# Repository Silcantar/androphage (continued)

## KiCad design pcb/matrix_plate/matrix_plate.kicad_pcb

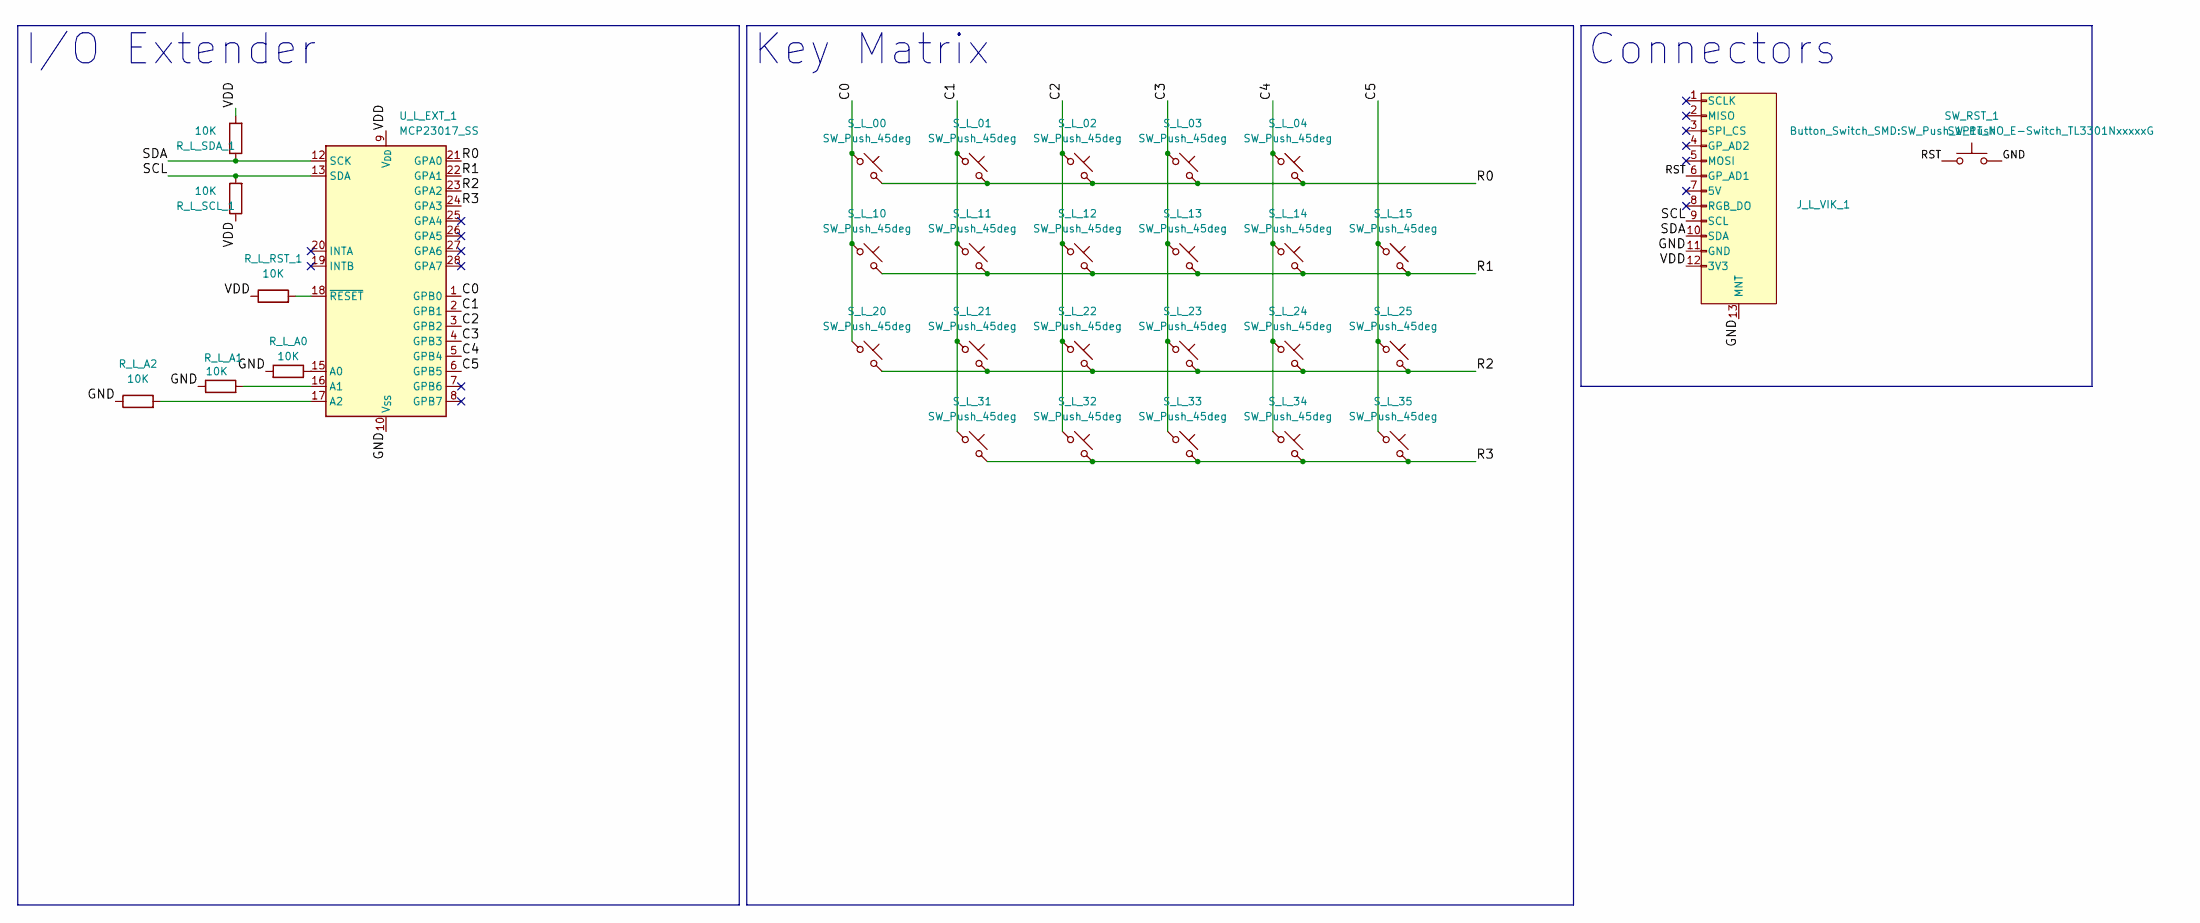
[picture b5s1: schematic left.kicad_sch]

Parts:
J_L_VIK_1: vik-module-connector; vik-module-connector-horizontal
R_L_A0, R_L_A1, R_L_A2: 10K; R_0805_2012Metric_Pad1.20x1.40mm_HandSolder
R_L_RST_1: 10K; R_0805_2012Metric_Pad1.20x1.40mm_HandSolder
R_L_SCL_1: 10K; R_0805_2012Metric_Pad1.20x1.40mm_HandSolder
R_L_SDA_1: 10K; R_0805_2012Metric_Pad1.20x1.40mm_HandSolder
SW_RST_1: SW_Push; SW_Push_1P1T_NO_E-Switch_TL3301NxxxxxG
S_L_00, S_L_01, S_L_02, S_L_03, S_L_04, S_L_10, S_L_11, S_L_12, S_L_13, S_L_14, S_L_15, S_L_20, S_L_21, S_L_22, S_L_23, S_L_24, S_L_25, S_L_31, S_L_32, S_L_33, S_L_34, S_L_35: SW_Push_45deg; SW_GLP_Kailh_Choc_V1V2_HotSwap_PTH
U_L_EXT_1: MCP23017_SS; SSOP-28_5.3x10.2mm_P0.65mm

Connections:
/Left/C0: S_L_00.1, S_L_10.1, S_L_20.1, U_L_EXT_1.1 (GPB0)
/Left/C1: S_L_01.1, S_L_11.1, S_L_21.1, S_L_31.1, U_L_EXT_1.2 (GPB1)
/Left/C2: S_L_02.1, S_L_12.1, S_L_22.1, S_L_32.1, U_L_EXT_1.3 (GPB2)
/Left/C3: S_L_03.1, S_L_13.1, S_L_23.1, S_L_33.1, U_L_EXT_1.4 (GPB3)
/Left/C4: S_L_04.1, S_L_14.1, S_L_24.1, S_L_34.1, U_L_EXT_1.5 (GPB4)
/Left/C5: S_L_15.1, S_L_25.1, S_L_35.1, U_L_EXT_1.6 (GPB5)
/Left/GND: J_L_VIK_1.11 (GND), J_L_VIK_1.13 (MNT), R_L_A0.2, R_L_A1.1, R_L_A2.1, SW_RST_1.2, U_L_EXT_1.10 (V_{SS})
/Left/R0: S_L_00.2, S_L_01.2, S_L_02.2, S_L_03.2, S_L_04.2, U_L_EXT_1.21 (GPA0)
/Left/R1: S_L_10.2, S_L_11.2, S_L_12.2, S_L_13.2, S_L_14.2, S_L_15.2, U_L_EXT_1.22 (GPA1)
/Left/R2: S_L_20.2, S_L_21.2, S_L_22.2, S_L_23.2, S_L_24.2, S_L_25.2, U_L_EXT_1.23 (GPA2)
/Left/R3: S_L_31.2, S_L_32.2, S_L_33.2, S_L_34.2, S_L_35.2, U_L_EXT_1.24 (GPA3)
/Left/RST: J_L_VIK_1.6 (GP_AD1), SW_RST_1.1
/Left/SCL: J_L_VIK_1.9 (SCL), R_L_SCL_1.2, U_L_EXT_1.13 (SDA)
/Left/SDA: J_L_VIK_1.10 (SDA), R_L_SDA_1.1, U_L_EXT_1.12 (SCK)
/Left/VDD: J_L_VIK_1.12 (3V3), R_L_RST_1.1, R_L_SCL_1.1, R_L_SDA_1.2, U_L_EXT_1.9 (V_{DD})
unnamed: R_L_A0.1, U_L_EXT_1.15 (A0)
unnamed: R_L_A1.2, U_L_EXT_1.16 (A1)
unnamed: R_L_A2.2, U_L_EXT_1.17 (A2)
unnamed: R_L_RST_1.2, U_L_EXT_1.18 (~RESET)

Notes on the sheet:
Connectors
Key Matrix
I/O Extender

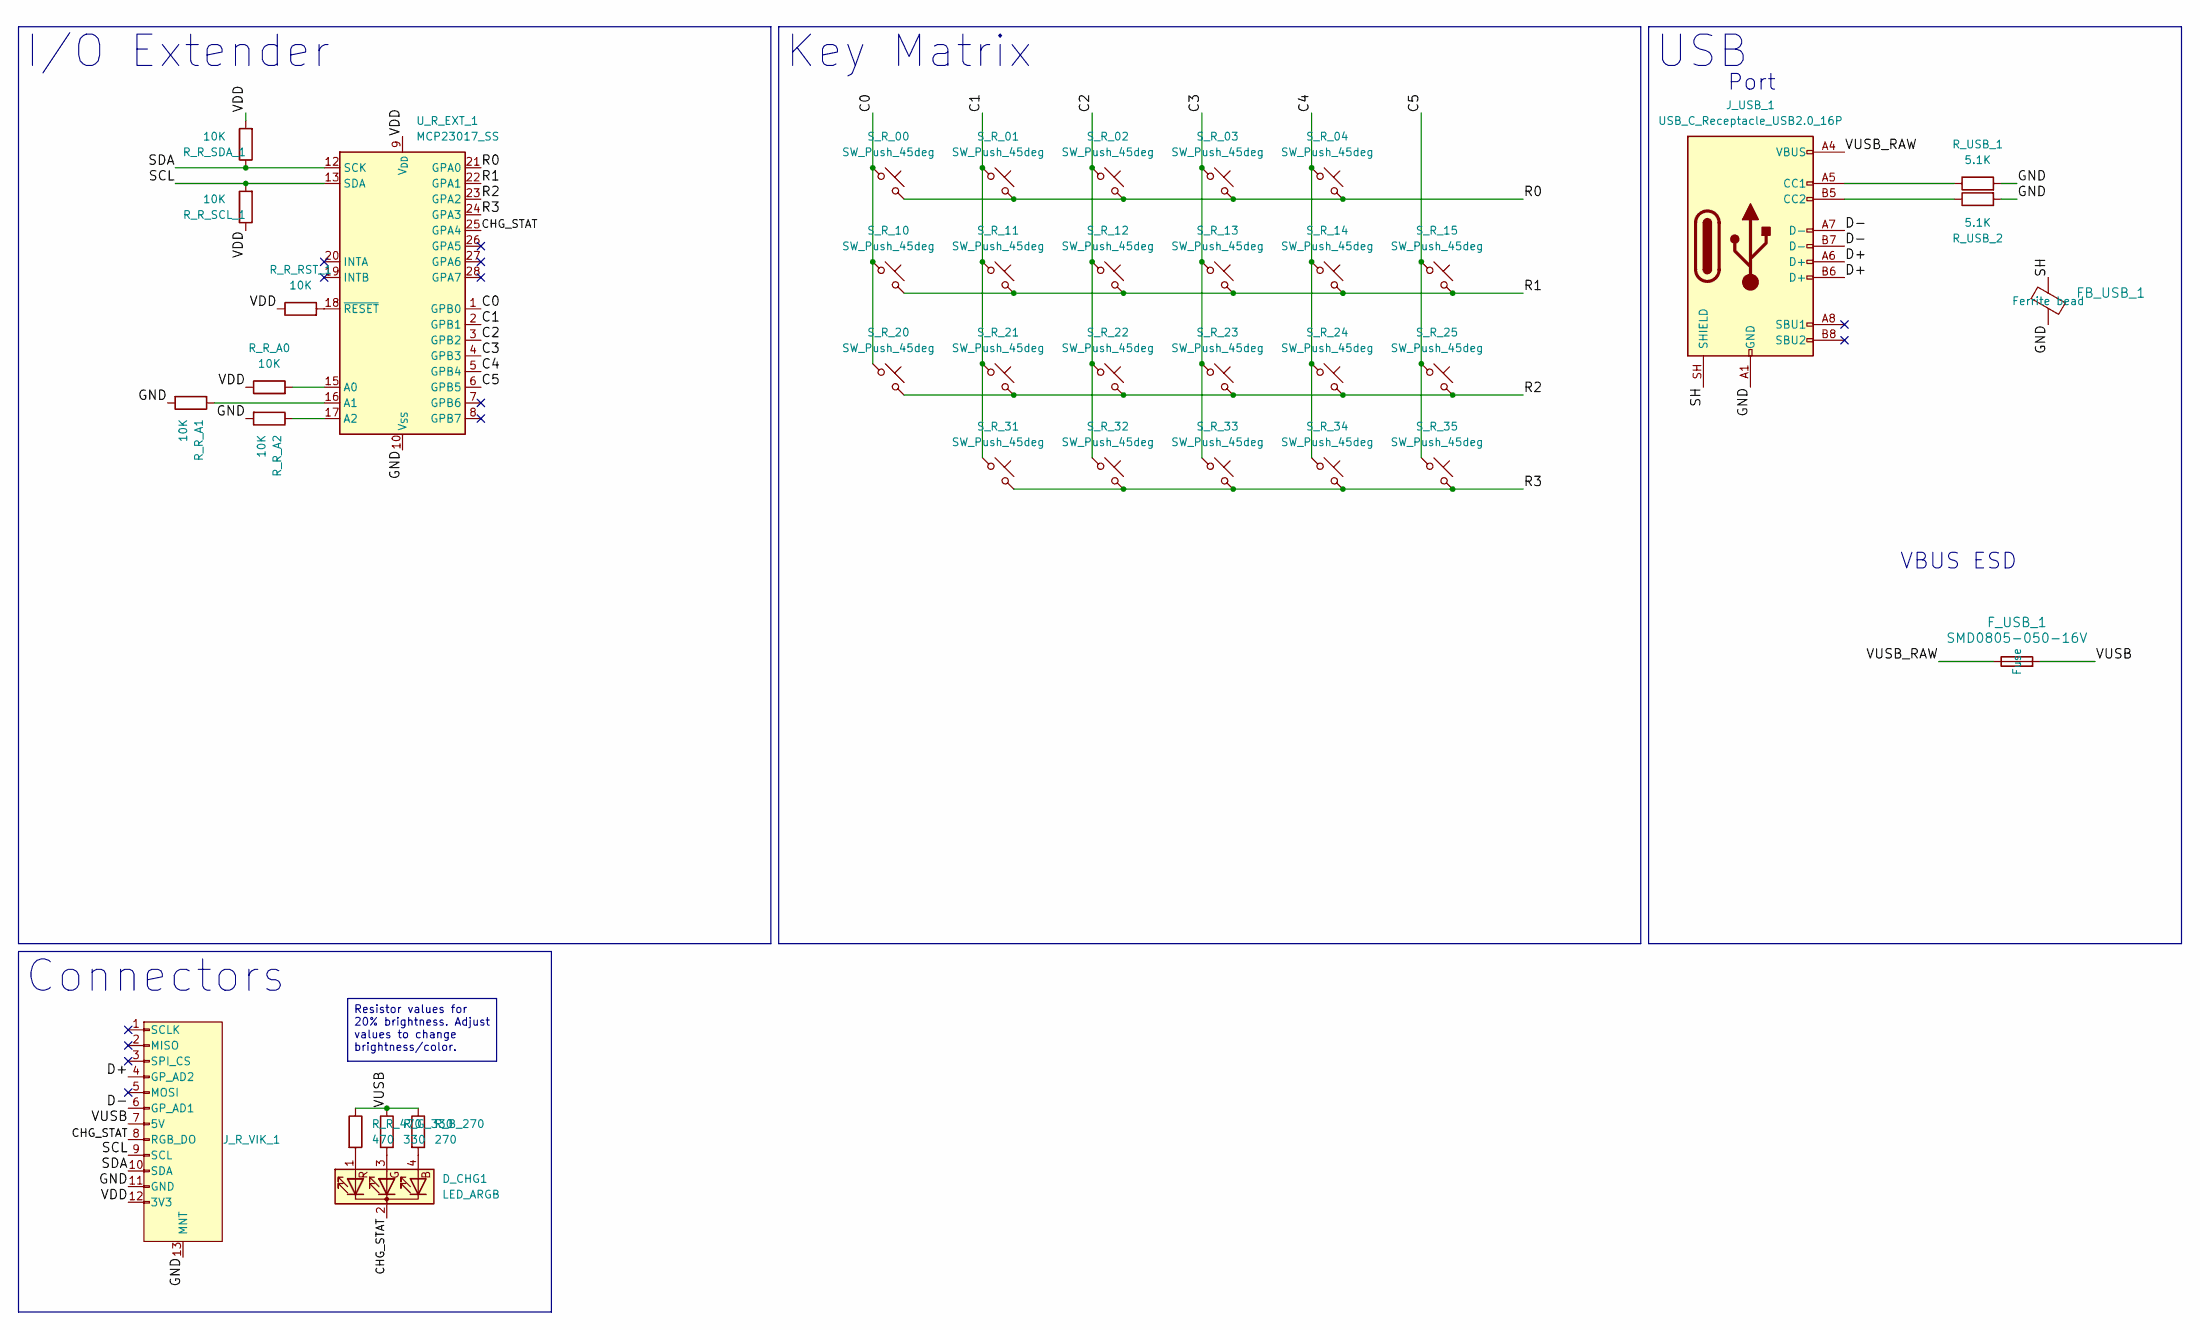
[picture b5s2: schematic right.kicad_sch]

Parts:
D_CHG1: LED_ARGB; LED_Kingbright_APFA3010_3x1.5mm_Horizontal
FB_USB_1: L_0805_2012Metric_Pad1.05x1.20mm_HandSolder; LCSC Part Number C21286
F_USB_1: SMD0805-050-16V; Fuse_0805_2012Metric_Pad1.15x1.40mm_HandSolder; Manufacturer Part Number SMD0805-050-16V; LCSC Part Number C2833485
J_R_VIK_1: vik-module-connector; vik-module-connector-horizontal
J_USB_1: USB_C_Receptacle_USB2.0_16P; USB_C_Receptacle_HRO_TYPE-C-31-M-12
R_B_270: 270; R_0805_2012Metric_Pad1.20x1.40mm_HandSolder
R_G_330: 330; R_0805_2012Metric_Pad1.20x1.40mm_HandSolder
R_R_470: 470; R_0805_2012Metric_Pad1.20x1.40mm_HandSolder
R_R_A0, R_R_A1, R_R_A2: 10K; R_0805_2012Metric_Pad1.20x1.40mm_HandSolder
R_R_RST_1: 10K; R_0805_2012Metric_Pad1.20x1.40mm_HandSolder
R_R_SCL_1: 10K; R_0805_2012Metric_Pad1.20x1.40mm_HandSolder
R_R_SDA_1: 10K; R_0805_2012Metric_Pad1.20x1.40mm_HandSolder
R_USB_1, R_USB_2: 5.1K; R_0805_2012Metric_Pad1.20x1.40mm_HandSolder
S_R_00, S_R_01, S_R_02, S_R_03, S_R_04, S_R_10, S_R_11, S_R_12, S_R_13, S_R_14, S_R_15, S_R_20, S_R_21, S_R_22, S_R_23, S_R_24, S_R_25, S_R_31, S_R_32, S_R_33, S_R_34, S_R_35: SW_Push_45deg; SW_GLP_Kailh_Choc_V1V2_HotSwap_PTH
U_R_EXT_1: MCP23017_SS; SSOP-28_5.3x10.2mm_P0.65mm

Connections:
/Right/C0: S_R_00.1, S_R_10.1, S_R_20.1, U_R_EXT_1.1 (GPB0)
/Right/C1: S_R_01.1, S_R_11.1, S_R_21.1, S_R_31.1, U_R_EXT_1.2 (GPB1)
/Right/C2: S_R_02.1, S_R_12.1, S_R_22.1, S_R_32.1, U_R_EXT_1.3 (GPB2)
/Right/C3: S_R_03.1, S_R_13.1, S_R_23.1, S_R_33.1, U_R_EXT_1.4 (GPB3)
/Right/C4: S_R_04.1, S_R_14.1, S_R_24.1, S_R_34.1, U_R_EXT_1.5 (GPB4)
/Right/C5: S_R_15.1, S_R_25.1, S_R_35.1, U_R_EXT_1.6 (GPB5)
/Right/CHG_STAT: D_CHG1.2 (K), J_R_VIK_1.8 (RGB_DO), U_R_EXT_1.25 (GPA4)
/Right/D+: J_R_VIK_1.4 (GP_AD2), J_USB_1.A6 (D+), J_USB_1.B6 (D+)
/Right/D-: J_R_VIK_1.6 (GP_AD1), J_USB_1.A7 (D-), J_USB_1.B7 (D-)
/Right/GND: FB_USB_1.2, J_R_VIK_1.11 (GND), J_R_VIK_1.13 (MNT), J_USB_1.A1 (GND), J_USB_1.A12 (GND), J_USB_1.B1 (GND), J_USB_1.B12 (GND), R_R_A1.2, R_R_A2.2, R_USB_1.2, R_USB_2.2, U_R_EXT_1.10 (V_{SS})
/Right/R0: S_R_00.2, S_R_01.2, S_R_02.2, S_R_03.2, S_R_04.2, U_R_EXT_1.21 (GPA0)
/Right/R1: S_R_10.2, S_R_11.2, S_R_12.2, S_R_13.2, S_R_14.2, S_R_15.2, U_R_EXT_1.22 (GPA1)
/Right/R2: S_R_20.2, S_R_21.2, S_R_22.2, S_R_23.2, S_R_24.2, S_R_25.2, U_R_EXT_1.23 (GPA2)
/Right/R3: S_R_31.2, S_R_32.2, S_R_33.2, S_R_34.2, S_R_35.2, U_R_EXT_1.24 (GPA3)
/Right/SCL: J_R_VIK_1.9 (SCL), R_R_SCL_1.2, U_R_EXT_1.13 (SDA)
/Right/SDA: J_R_VIK_1.10 (SDA), R_R_SDA_1.1, U_R_EXT_1.12 (SCK)
/Right/SH: FB_USB_1.1, J_USB_1.SH (SHIELD)
/Right/VDD: J_R_VIK_1.12 (3V3), R_R_A0.1, R_R_RST_1.1, R_R_SCL_1.1, R_R_SDA_1.2, U_R_EXT_1.9 (V_{DD})
/Right/VUSB: F_USB_1.2, J_R_VIK_1.7 (5V), R_B_270.1, R_G_330.1, R_R_470.1
/Right/VUSB_RAW: F_USB_1.1, J_USB_1.A4 (VBUS), J_USB_1.A9 (VBUS), J_USB_1.B4 (VBUS), J_USB_1.B9 (VBUS)
unnamed: D_CHG1.4 (BA), R_B_270.2
unnamed: D_CHG1.3 (GA), R_G_330.2
unnamed: D_CHG1.1 (RA), R_R_470.2
unnamed: J_USB_1.A5 (CC1), R_USB_1.1
unnamed: J_USB_1.B5 (CC2), R_USB_2.1
unnamed: R_R_A0.2, U_R_EXT_1.15 (A0)
unnamed: R_R_A1.1, U_R_EXT_1.16 (A1)
unnamed: R_R_A2.1, U_R_EXT_1.17 (A2)
unnamed: R_R_RST_1.2, U_R_EXT_1.18 (~RESET)

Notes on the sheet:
VBUS ESD
Port
Connectors
USB
I/O Extender
Key Matrix
Resistor values for 20% brightness. Adjust values to change brightness/color.

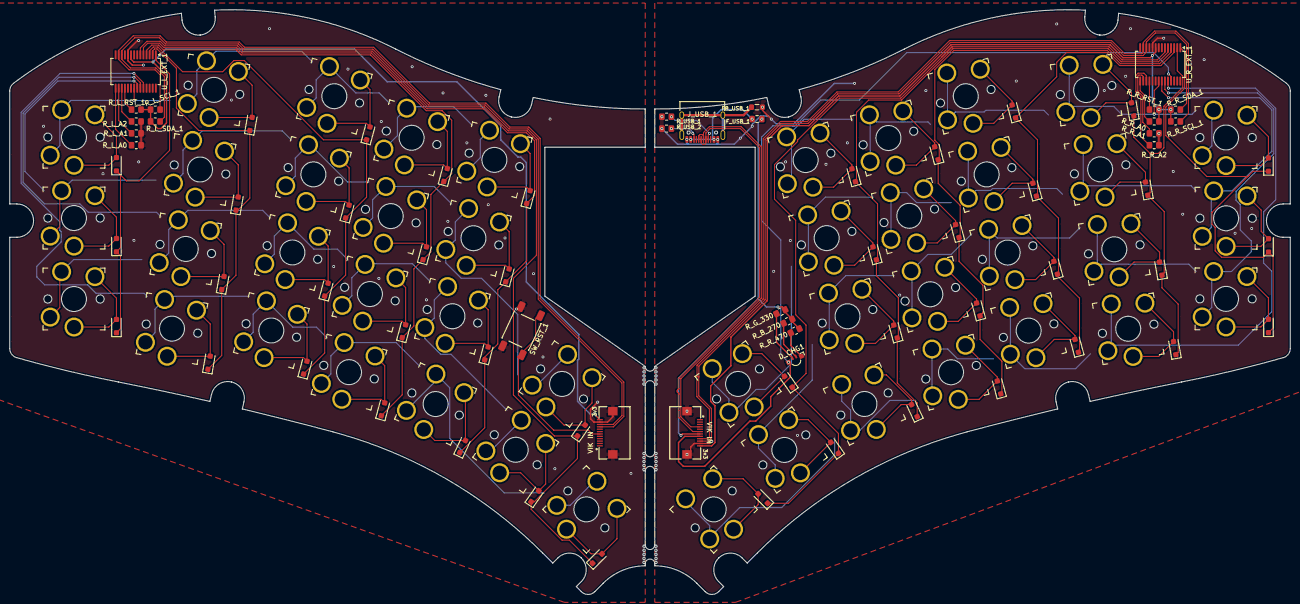
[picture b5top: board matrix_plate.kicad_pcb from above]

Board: 2 copper layers, 269.2 x 122.9 mm, 70 parts (0 on the bottom side), 48 nets.

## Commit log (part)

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2025-11-24 Initial Commit.
2025-11-27 Work on PCBs.
2025-11-28 Replace KB2040 with XIAO nRF, work on PCB routing.
2025-12-10 Clean up folder structure.
2025-12-11 Work on case.
2025-12-11 Create VIK hat for Seeed Xiao nRF.
2025-12-13 Tentatively finish PCB design.
2025-12-16 Work on mechanical design.
2025-12-18 Change VIK submodule to the dev branch of my fork to include the modules developed for this project.
2025-12-18 Change license from GPLv3 to CERN-OHL-Sv2.
2025-12-18 Parametrize mechanical design.
2025-12-19 - Tentatively finish switch and top plates. - Add BOSL as submodule.
2025-12-19 Rename BOSL to BOSL2.
2025-12-19 Refactor basically everything.
2025-12-30 Expose plate sketch points as functions.
2026-01-01 Updated VIK.
2026-01-06 Refactor parameters to not use objects.
2026-01-07 Finish refactoring.
2026-01-07 More refactoring.
2026-01-10 Remove BOSL2 submodule.
2026-01-12 Increase tent to 7 degrees.
2026-01-20 Remove BOSL again.
2026-01-23 Add thumb cluster notch to frame.
2026-01-23 Clean up CAD files.
2026-01-23 Work on path framework to reconcile plates with frame.
2026-01-23 Update documentation.
2026-01-24 Finish the necessary parts of the path library.
2026-01-24 Update BOM.
2026-01-25 Remove cad/library folder and re-add it as a submodule.
2026-01-25 Fix hard-coded notch cutter dimension.
2026-01-25 Move items to openscad_library.
2026-01-25 Start converting bottom plate to use path library.
2026-01-25 Rename some hinge parameters.
2026-01-25 Start refactoring to re-enable Configurator, reduce file size, and improve modularity.
2026-01-26 Move global declarations to separate file.
2026-01-26 Move parameter calculations to separate file.
2026-01-26 Start updating component files with new structure.
2026-01-26 Add missing parameters to objects.
2026-01-26 Update more components with new structure.
2026-01-27 Change indentation to spaces.
2026-01-27 Minor reorganization of definitions.
2026-01-27 Update library.
2026-01-27 More minor definition reorganization.
2026-01-27 Update banner image.
2026-01-28 Add quote to readme.
2026-01-28 Add cluster cutout parameter.
2026-01-28 Unify plate and PCB code.
2026-01-28 Start updating main files with new structure.
2026-01-29 Change from using "use" to import components to using "include". Remove circular includes.
2026-01-29 Update components to reflect the use of "include" rather than "use".
2026-01-30 Add OpenSCAD configurator JSON.
2026-01-30 Revert to non-object parameters.
2026-02-01 Fix misalignment of plates and frame.
2026-02-01 Clean up dead code.
2026-02-01 Add cutouts to plates for trackball & sensor.
2026-02-01 Fix cutouts in center block for hinges and top plate.
2026-02-01 Adjust magnetic connector placement, add cutout to PCB and switch plate.
2026-02-01 Add fillets to LED holes.
2026-02-02 Clean up dead code in androphage.scad.
2026-02-02 Fix key cutouts in hinge.
2026-02-03 Add USB cutout to MCU.
2026-02-03 Remove KLP Lamé submodule.
2026-02-03 Fix frame height.
2026-02-03 Remove switch STL.
2026-02-03 Remove KLP Lamé from .gitmodules.
2026-02-03 Add keycaps submodule.
2026-02-03 Update keycaps submodule.
2026-02-03 Start rewriting key placement module.
2026-02-08 Add compile script.
2026-02-08 Update keycaps and library submodules.
2026-02-09 Update submodules.
2026-02-09 Rewrite switch and keycap placement code.
2026-02-10 Add PCB submodules.
2026-02-10 Move old PCB files to "old" folder.
2026-02-11 Re-create KiCAD project.
2026-02-11 - Adapt nrfmicro schematic for control and power components. - Copy key matrix schematics from old KiCAD project.
2026-02-11 Complete preliminary PCB schematic.
2026-02-12 Add KiCAD backup files to gitignore.
2026-02-12 Add option to export switch plate sketch DXF for PCB design.
2026-02-12 Start PCB layout.
2026-02-12 Move old KiCAD files to old folder.
2026-02-12 Start adding support for column splay.
2026-02-16 Add BOSL2 as submodule.
2026-02-18 Add compiles OpenSCAD files to gitignore.
2026-02-18 Update BOSL2.
2026-02-18 Update compile.sh.
2026-02-18 Start BOSL-based plate and frame outline.
2026-02-19 Add ergogen json file.
2026-02-19 Create script for converting Ergogen YAML to OpenSCAD.
2026-02-20 Start PythonSCAD project.
2026-02-22 Refine battery component; start BTU component.
2026-02-23 Add .venv to gitignore.
2026-02-23 Start cadQuery project.
2026-02-24 Start Build123d project.
2026-02-24 Move OpenSCAD project to corresponding folder.
2026-02-24 Rename build123d to cad.
2026-02-24 Finish battery and BTU components; start key placement module.
2026-02-26 Start writing code to convert ergogen yaml to key placement.
2026-02-27 Work on key placement.
2026-03-03 Work on key locations.
2026-03-04 Remove old submodule folders.
2026-03-04 Finish key locations.
2026-03-08 Refine key locations code.
2026-03-11 Start writing code to generate plate outline.
2026-03-11 Refine plate outline.
2026-03-12 Continue working on plate outline.
2026-03-14 - Rename androphage_common to common. - Simplify Component subclasses by passing kwargs to super().__init__().
2026-03-14 Create parameter-parsing code.
2026-03-14 Start writing code to generate the plates.
2026-03-15 - Move key_locations and plate_outline functions to the Androphage class. - Adapt said functions to use parameters read from YAML file. - Add initialization methods to Androphage class.
2026-03-16 Continue working on plate code.
2026-03-17 Add edge and center width to plates.
2026-03-18 Add cutout to top plate.
2026-03-21 Add trackball cutout and some fillets to top plate.
2026-03-22 Deprecate key_locations test (superceded by test_layout parameter in androphage class).
2026-03-22 Add colors to YAML config file.
2026-03-22 Start developing center block component.
2026-03-23 Add trackball case to center block.
2026-03-23 Start adding BTU sockets to center block.
2026-03-25 Refactor BTU module to use common interface.
2026-03-25 Reformat YAML to snake_case.
2026-03-25 Update rest of project to match snake_case YAML file.
2026-03-25 Minor changes to BTU module.
2026-03-25 Use YAML aliases to define BTU type.
2026-03-25 Refine BTU placement.
2026-03-25 Add magnetic connector module.
2026-03-25 Add trackball sensor module.
2026-03-26 Add sensor holder, magnetic connector cutout, and prototype screw bosses to center block.
2026-03-28 Create frame module.
2026-03-30 Move center width extrusion logic to the outline method.
2026-03-31 Better alphabetize androphage.yaml.
2026-03-31 Change BTU models from derived classes to class methods of the BTU class.
2026-03-31 Align plate front center corner with origin and fix a few bugs.
2026-03-31 Add angle to ends of frame.
2026-03-31 Update center block to match changes to BTU.
2026-03-31 Add missing parameters.
2026-03-31 Start writing the assembly code.
2026-04-01 Start rewriting component classes to use the parameter object rather than a ton of arguments.
2026-04-02 Continue rewriting component classes to use parameters.
2026-04-04 Clean up code.
2026-04-04 Update components to use color from the YAML file.
2026-04-04 Update components to use parameters object.
2026-04-04 Update component calls in the main file to use parameters object.
2026-04-04 FIx "cannot pickle" error.
2026-04-05 Add parameters to yaml file for calculating key height.
2026-04-08 Make case height driven by the key height or trackball radius, whichever is greater.
2026-04-08 Move layout function to layout module.
2026-04-09 Add switch, PCB, and bottom plates to assembly.
2026-04-09 Fix collisions between frame and center block.
2026-04-10 Start removing collisions between plates and center block.
2026-04-10 Add case production files.
2026-04-12 Add cutout for trackball sensor to pcb and switch plate.
2026-04-18 Add Build123d as a submodule.
2026-04-18 Add fillets to plates.
2026-04-18 Fix frame screw locations.
2026-04-20 Add clearance between frame and PCB/switch plate.
2026-04-20 Move frame screw location definition to layout module.
2026-04-20 Add cutouts for frame screw bosses to PCB and switch plate.
2026-04-30 Update build123d submodule.
2026-04-30 Add magnetic connector to assembly.
2026-04-30 Add holes for countersink screws to bottom plate.
2026-04-30 Fix frame location.
2026-04-30 Change top plate trackball cutout from cylindrical to spherical.
2026-04-30 Add trackball sensor to assembly.
2026-05-01 Add hinge.
2026-05-01 Add additional screw sizes.
2026-05-01 Fix position of hinge cutouts.
2026-05-01 Adjust sensor cutout in plates.
2026-05-01 Fix BTU labels.
2026-05-01 Add right half.
2026-05-01 Start adding thumb notch to frame.
2026-05-04 Add fillet to top plate cutouts.
2026-05-05 Add layout files for ordering from 3dKeycap.
2026-05-05 Adjust keyboard height.
2026-05-05 Start designing base component.
2026-05-06 Fix draft operation in center block.
2026-05-06 Add hinge motion to assembly.
2026-05-06 Further develop base.
2026-05-06 Update readme.
2026-05-06 Clean up frame code.
2026-05-07 Add parameters for magnets.
2026-05-07 Remove OpenSCAD and other deprecated files.
2026-05-11 Start designing custom knife hinge.
2026-05-11 Add bd_keyboard submodule.
2026-05-12 Refactor key placement code.
2026-05-12 Fix magnetic connector lip location.
2026-05-12 Move derived parameter calculations from parameter module to layout module to avoid circular import.
2026-05-12 Add USB connector.
2026-05-12 Redesign knife hinge.
2026-05-12 Make knife hinge parametric.
2026-05-13 Harmonize screw parameter naming.
2026-05-13 Add plate DXF export code.
2026-05-13 Remove OpenSCAD polders (again?)
2026-05-13 Update bd_keyboard.
2026-05-13 Add knife hinges to assembly.
2026-05-13 Add hinge cutouts to center block.
2026-05-14 Update key switch footprint.
2026-05-14 Remove Build123d submodule.
2026-05-14 FIx plate DXF export.
2026-05-14 Restart PCB design.
2026-05-15 Refactor plate module to use algebra mode.
2026-05-15 Refactor center block module to use algebra mode.
2026-05-16 Refactor frame module to use algebra mode.
2026-05-18 Update size of magnetic connector and trackball sensor PCBs to reflect updated VIK modules.
2026-05-18 Relocate USB connector to switch PCB.
2026-05-18 Refine USB port placement.
2026-05-20 Split PCBs into separate projects.
2026-05-21 Redo matrix plates.
2026-05-21 Start redoing bottom plate.
2026-05-21 Update PCB components.
2026-05-22 Rename pcb_plate to matrix_plate.
2026-05-22 Adjust USB position.
2026-05-22 Tentatively finish PCBs.
2026-05-23 Update PCB production files.
2026-05-24 Add screw hole to trackball sensor model.
2026-05-24 Add the rest of the hinge parts to the assembly.
2026-05-24 Expand hinge production file script to export DXFs and multi-part STEP.
2026-05-25 Start developing new base.
2026-05-25 Add more KiCAD files to gitignore.
2026-05-26 Add fillets to hinges to improve machinability.
2026-05-26 Work on base.
2026-05-27 Tentatively finish base.
2026-05-30 Add dependencies to pyproject.toml.
2026-05-30 Remove VSCode files and add them to gitignore.
2026-05-30 Fix minor build issues.
2026-05-30 Start rewriting the assembly code to make animating movement easier.
2026-05-30 Start silkscreen art for bottom PCB.
2026-05-31 Work on assembly code.
2026-06-06 Re-integrate eye code into base module.
2026-06-06 Finish refactoring assembly code.
2026-06-06 Make build script more robust.
2026-06-08 Refactor magnetic connector and add joints.
2026-06-08 Fix PCB and switch plate positioning.
2026-06-08 Add battery to assembly.
2026-06-18 Create screen component.
2026-06-18 Add ESD protection to PCBs.
2026-06-18 Add screen cutout to top plate.
2026-06-19 Add Nice!View screen to assembly.
2026-06-19 Remove old PCB files.
2026-06-19 Remove more old PCB files.
2026-06-19 Specify branch of key-switches as lopro-hybrids in .gitmodules.
2026-06-22 Add hinges to assembly.
2026-06-24 Move battery module to bd_keyboard.
2026-06-24 Update assembly code to use bd_keyboard battery.
2026-06-24 Adjust base shape for better stability.
2026-06-25 Finish base redesign.
2026-06-25 Add heyitscassio's fork of PeudoMakeMeKeycapProfiles as a submodule.
2026-06-25 Add key switches to assembly.
2026-06-25 Remove PseudoMakeMeKeycapProfiles submodule.
2026-06-25 Add keycap module.
2026-06-28 Add setup scripts.
2026-06-29 Change base trackball case shape to allow for foam filling.
